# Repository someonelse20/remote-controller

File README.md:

# remote-controller
Custom remote controler with esp32 to stream telemetry.

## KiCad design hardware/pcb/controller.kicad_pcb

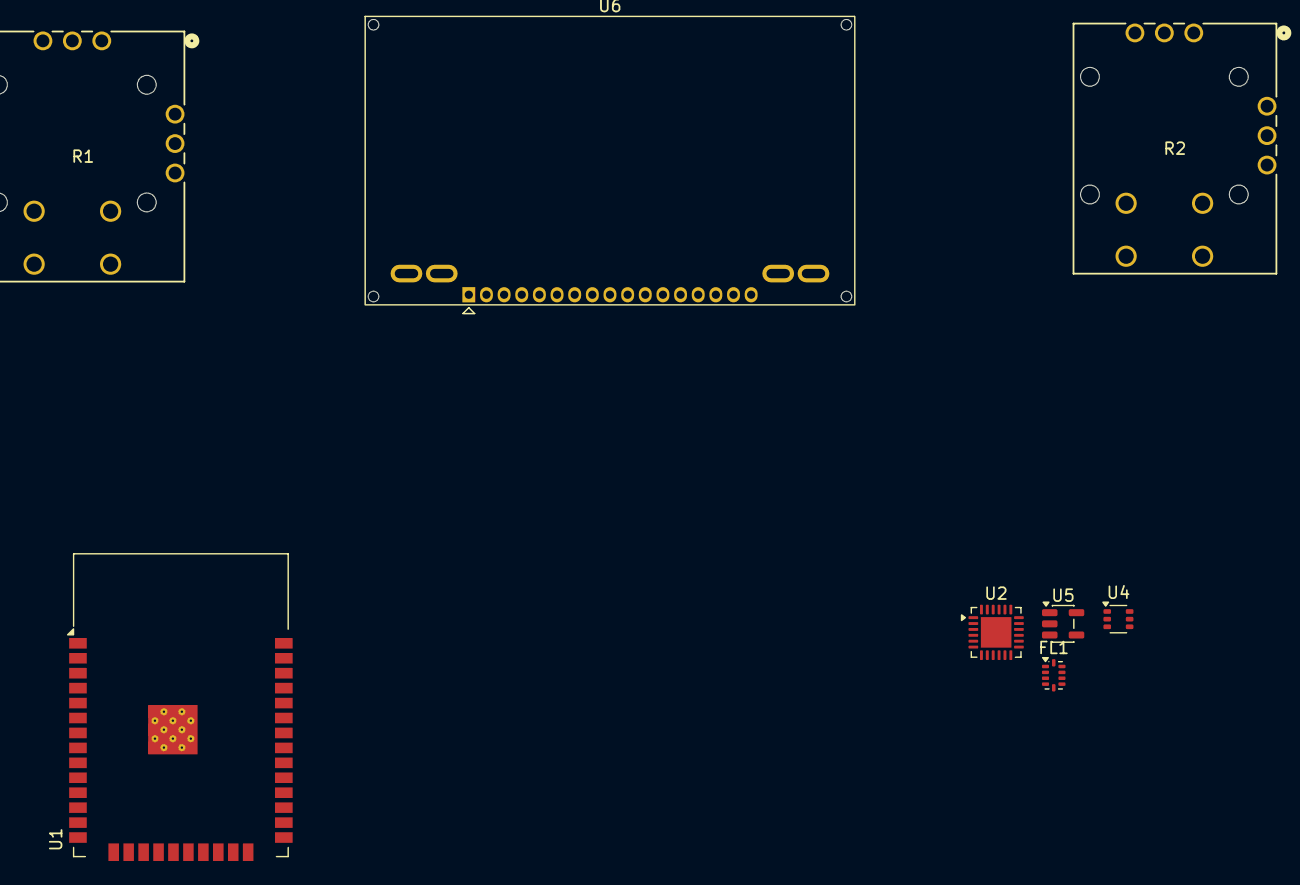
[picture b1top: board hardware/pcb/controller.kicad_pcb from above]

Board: 2 copper layers, 8 parts (0 on the bottom side), 3 nets, no tracks yet.

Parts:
FL1: 0900FM15K0039; Balun_Johanson_0900FM15K0039
R1, R2: THB001P; THB001P_CNK
U1: ESP32-WROOM-32
U2: SX1262IMLTRT; QFN-24-1EP_4x4mm_P0.5mm_EP2.6x2.6mm
U4: PE4259; SOT-363_SC-70-6
U5: AP2112K-3.3; SOT-23-5
U6: NHD-C12832A1Z-FSRGB

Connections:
unnamed: FL1.2 (GND), FL1.5 (GND), FL1.7 (GND), FL1.9 (GND), FL1.10 (GND)
unnamed: U1.1 (GND), U1.15 (GND), U1.38 (GND), U1.39 (GND)
unnamed: U2.2 (GND), U2.5 (GND), U2.8 (GND), U2.20 (GND), U2.25 (GND)

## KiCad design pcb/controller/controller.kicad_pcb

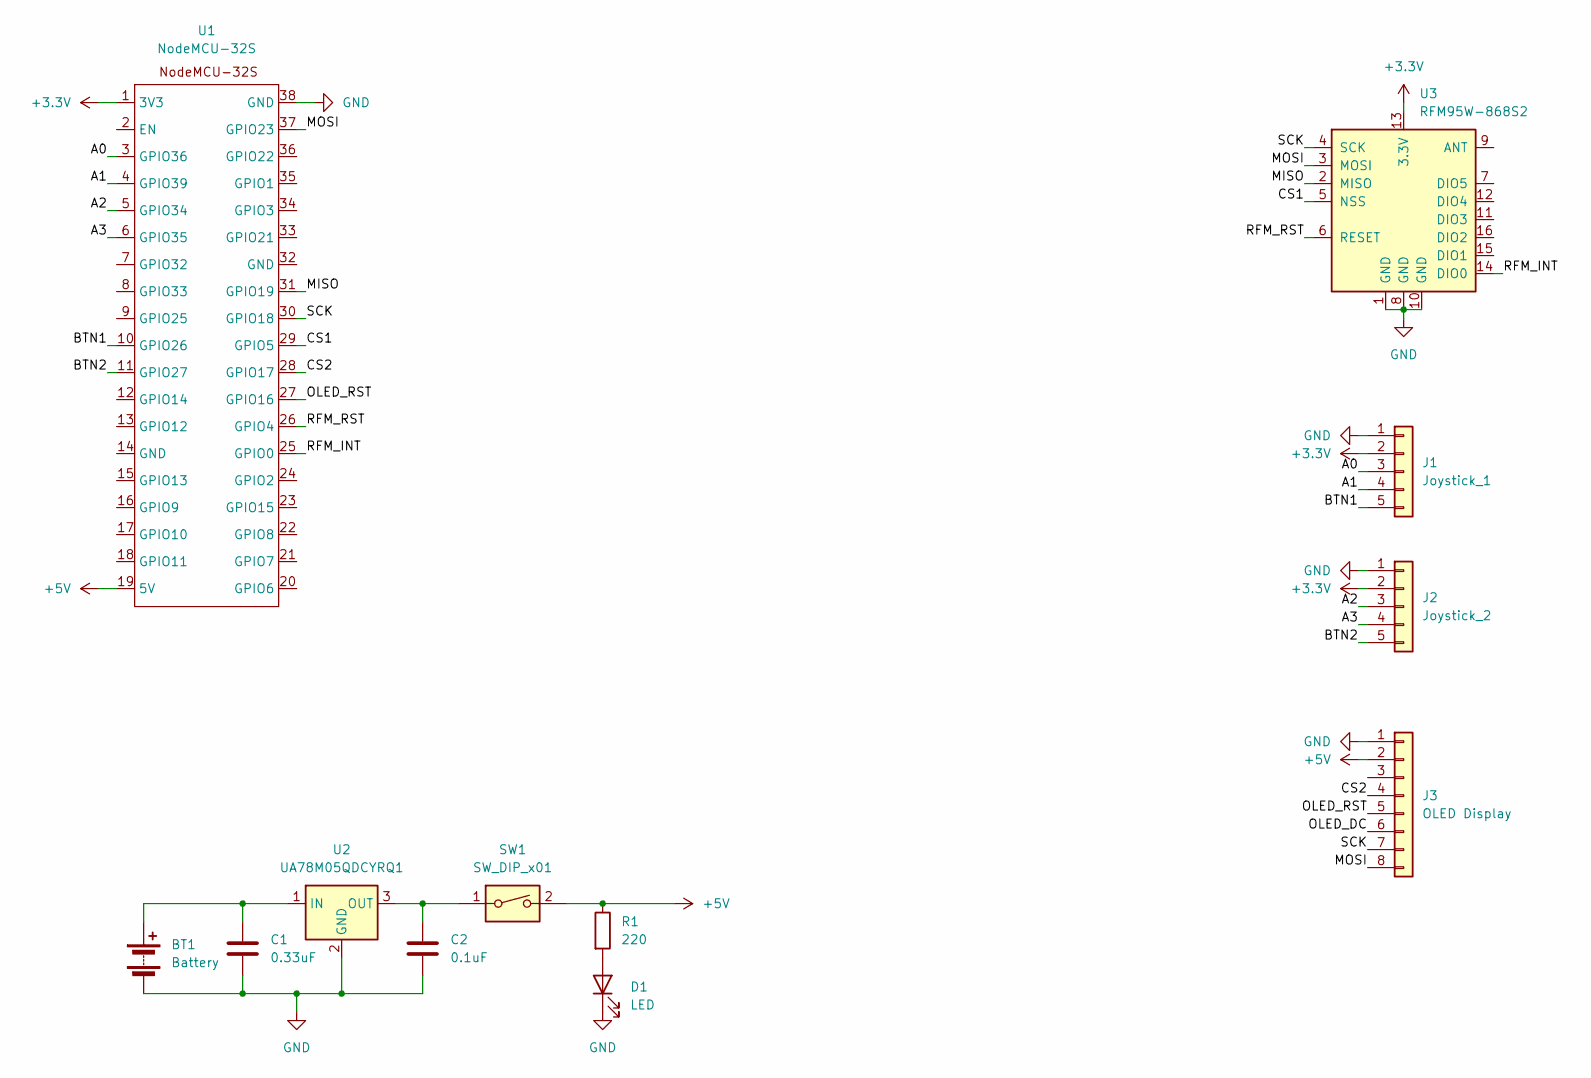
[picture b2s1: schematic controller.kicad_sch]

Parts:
BT1: Battery; PinHeader_1x02_P2.54mm_Vertical
C1: 0.33uF; C_0603_1608Metric_Pad1.08x0.95mm_HandSolder
C2: 0.1uF; C_0603_1608Metric_Pad1.08x0.95mm_HandSolder
D1: LED; LED_D5.0mm
J1: Joystick_1; PinHeader_1x05_P2.54mm_Vertical
J2: Joystick_2; PinHeader_1x05_P2.54mm_Vertical
J3: OLED Display; PinHeader_1x08_P2.54mm_Vertical
R1: 220; R_0603_1608Metric_Pad0.98x0.95mm_HandSolder
SW1: SW_DIP_x01; PinHeader_1x02_P2.54mm_Vertical
U1: NodeMCU-32S
U2: UA78M05QDCYRQ1; SOT-223-3_TabPin2
U3: RFM95W-868S2; HOPERF_RFM9XW_THT

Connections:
+3.3V: J1.2, J2.2, U1.1 (3V3), U3.13 (3.3V)
+5V: J3.2, R1.1, SW1.2, U1.19 (5V)
/A0: J1.3, U1.3 (GPIO36)
/A1: J1.4, U1.4 (GPIO39)
/A2: J2.3, U1.5 (GPIO34)
/A3: J2.4, U1.6 (GPIO35)
/BTN1: J1.5, U1.10 (GPIO26)
/BTN2: J2.5, U1.11 (GPIO27)
/CS1: U1.29 (GPIO5), U3.5 (NSS)
/CS2: J3.4, U1.28 (GPIO17)
/MISO: U1.31 (GPIO19), U3.2 (MISO)
/MOSI: J3.8, U1.37 (GPIO23), U3.3 (MOSI)
/OLED_DC: J3.6
/OLED_RST: J3.5, U1.27 (GPIO16)
/RFM_INT: U1.25 (GPIO0), U3.14 (DIO0)
/RFM_RST: U1.26 (GPIO4), U3.6 (RESET)
/SCK: J3.7, U1.30 (GPIO18), U3.4 (SCK)
GND: BT1.2 (-), C1.2, C2.2, D1.1 (K), J1.1, J2.1, J3.1, U1.38 (GND), U2.2 (GND), U3.1 (GND), U3.8 (GND), U3.10 (GND)
unnamed: BT1.1 (+), C1.1, U2.1 (IN)
unnamed: D1.2 (A), R1.2
unnamed: C2.1, SW1.1, U2.3 (OUT)

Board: 2 copper layers, 12 parts (1 on the bottom side), 20 nets, no tracks yet.

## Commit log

2026-02-03 added esp32 to schematic
2026-02-03 starting controller pcb
2026-02-04 working on pcb
2026-02-05 switched to node mcu
2026-02-07 redesigned schematic
